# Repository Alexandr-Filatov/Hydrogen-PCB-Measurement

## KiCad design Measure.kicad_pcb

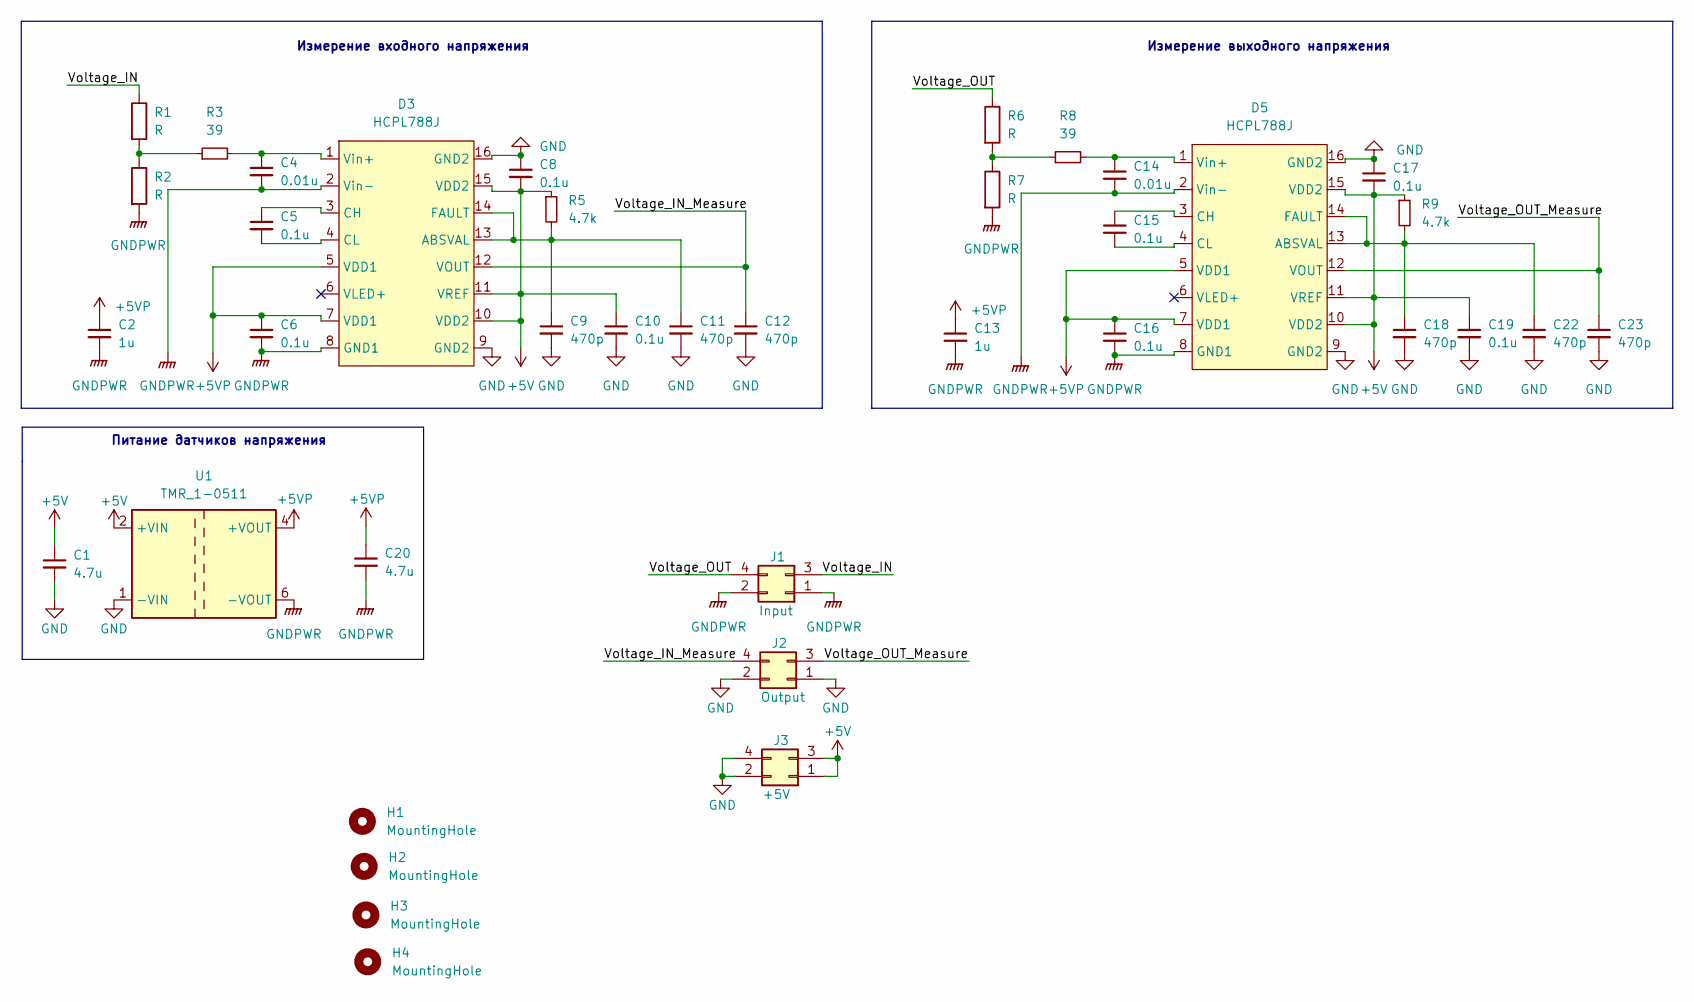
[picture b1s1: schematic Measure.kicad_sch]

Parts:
C1, C20: 4.7u; C_1210_3225Metric_Pad1.33x2.70mm_HandSolder
C2, C13: 1u; C_0805_2012Metric_Pad1.18x1.45mm_HandSolder
C4, C14: 0.01u; C_0805_2012Metric_Pad1.18x1.45mm_HandSolder
C5, C6, C8, C10, C15, C16, C17, C19: 0.1u; C_0805_2012Metric_Pad1.18x1.45mm_HandSolder
C9, C11, C12, C18, C22, C23: 470p; C_0805_2012Metric_Pad1.18x1.45mm_HandSolder
D3, D5: HCPL788J; SOIC-16W_7.5x10.3mm_P1.27mm
H1, H2, H3, H4: MountingHole; MountingHole_3.2mm_M3
J1: Input; Molex_Micro-Fit_3.0_43045-0400_2x02_P3.00mm_Horizontal
J2: Output; Molex_Micro-Fit_3.0_43045-0400_2x02_P3.00mm_Horizontal
J3: +5V; Molex_Micro-Fit_3.0_43045-0400_2x02_P3.00mm_Horizontal
R1, R2, R6, R7: R; R_2512_6332Metric_Pad1.40x3.35mm_HandSolder
R3, R8: 39; R_0805_2012Metric_Pad1.20x1.40mm_HandSolder
R5, R9: 4.7k; R_0805_2012Metric_Pad1.20x1.40mm_HandSolder
U1: TMR_1-0511; Converter_DCDC_TRACO_TMR-1-xxxx_Single_THT

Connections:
+5V: C1.1, C8.2, C10.1, C17.2, C19.1, D3.10 (VDD2), D3.11 (VREF), D3.15 (VDD2), D5.10 (VDD2), D5.11 (VREF), D5.15 (VDD2), J3.1, J3.3, R5.1, R9.1, U1.2 (+VIN)
+5VP: C2.1, C6.1, C13.1, C16.1, C20.1, D3.5 (VDD1), D3.7 (VDD1), D5.5 (VDD1), D5.7 (VDD1), U1.4 (+VOUT)
/Voltage_IN: J1.3, R1.1
/Voltage_IN_Measure: C12.1, D3.12 (VOUT), J2.4
/Voltage_OUT: J1.4, R6.1
/Voltage_OUT_Measure: C23.1, D5.12 (VOUT), J2.3
GND: C1.2, C8.1, C9.2, C10.2, C11.2, C12.2, C17.1, C18.2, C19.2, C22.2, C23.2, D3.9 (GND2), D3.16 (GND2), D5.9 (GND2), D5.16 (GND2), J2.1, J2.2, J3.2, J3.4, U1.1 (-VIN)
GNDPWR: C2.2, C4.2, C6.2, C13.2, C14.2, C16.2, C20.2, D3.2 (Vin-), D3.8 (GND1), D5.2 (Vin-), D5.8 (GND1), J1.1, J1.2, R2.2, R7.2, U1.6 (-VOUT)
unnamed: C4.1, D3.1 (Vin+), R3.2
unnamed: C5.1, D3.3 (CH)
unnamed: C5.2, D3.4 (CL)
unnamed: C9.1, C11.1, D3.13 (ABSVAL), D3.14 (FAULT), R5.2
unnamed: C14.1, D5.1 (Vin+), R8.2
unnamed: C15.1, D5.3 (CH)
unnamed: C15.2, D5.4 (CL)
unnamed: C18.1, C22.1, D5.13 (ABSVAL), D5.14 (FAULT), R9.2
unnamed: R1.2, R2.1, R3.1
unnamed: R6.2, R7.1, R8.1

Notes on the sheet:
Питание датчиков напряжения
Измерение входного напряжения
Измерение выходного напряжения

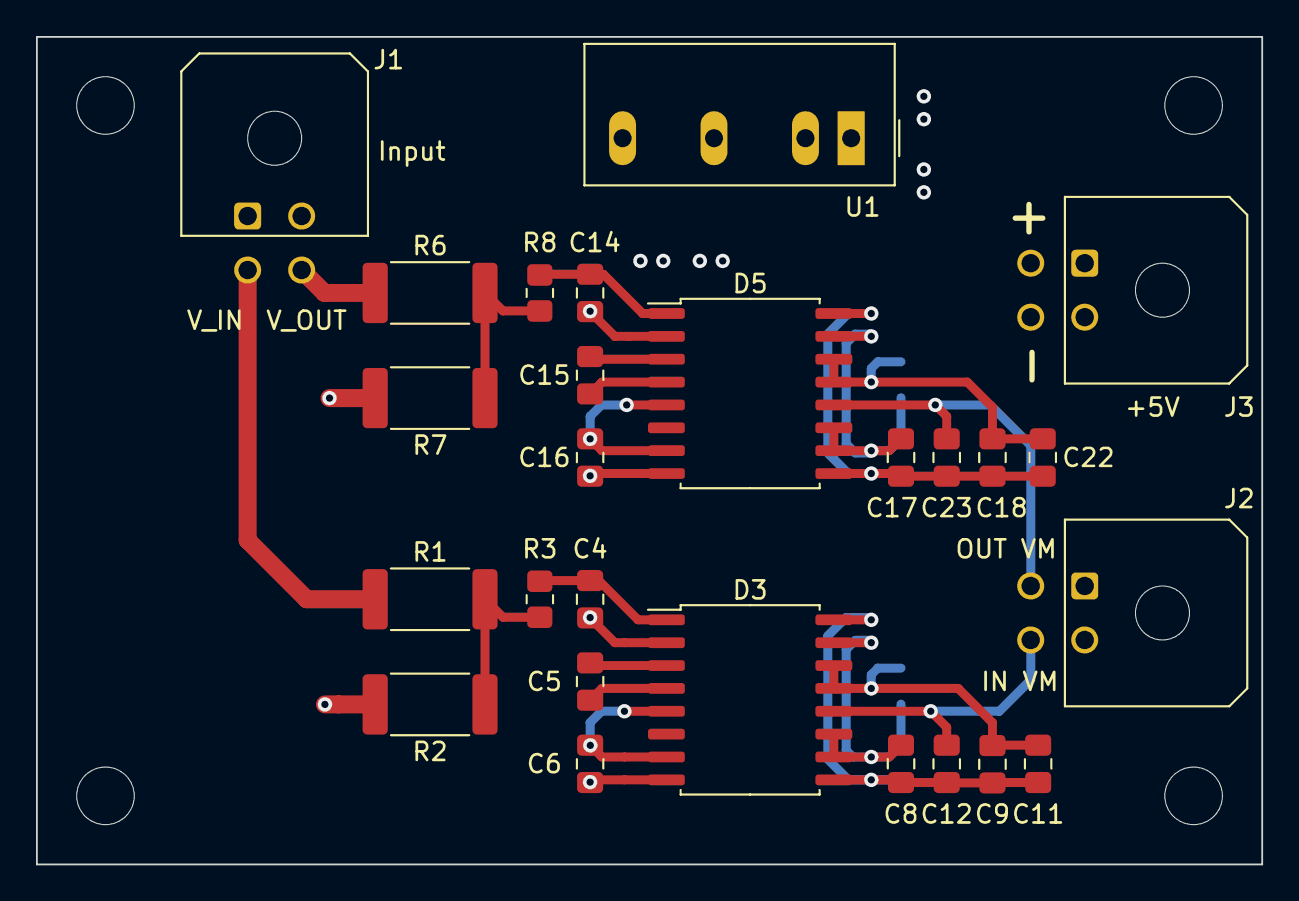
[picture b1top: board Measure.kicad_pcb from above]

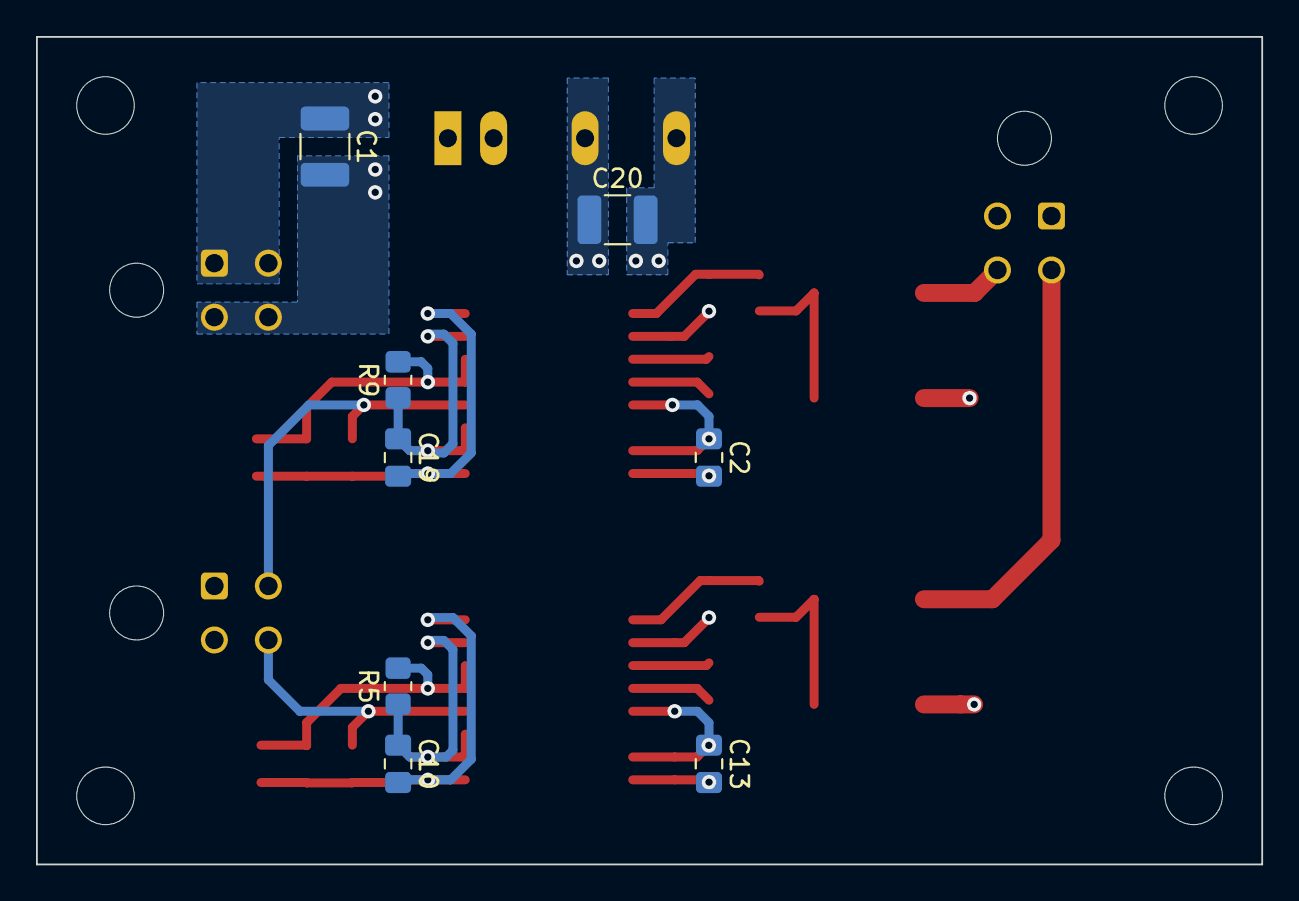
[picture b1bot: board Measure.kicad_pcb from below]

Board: 4 copper layers, 68.1 x 46.0 mm, 38 parts (8 on the bottom side), 18 nets.

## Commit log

2022-05-27 VER1.0
2022-06-02 Первая версия в производство
2022-08-15 Исправлены ошибки с неподключённым IN- и питанием
2022-08-15 Добавил гербера
